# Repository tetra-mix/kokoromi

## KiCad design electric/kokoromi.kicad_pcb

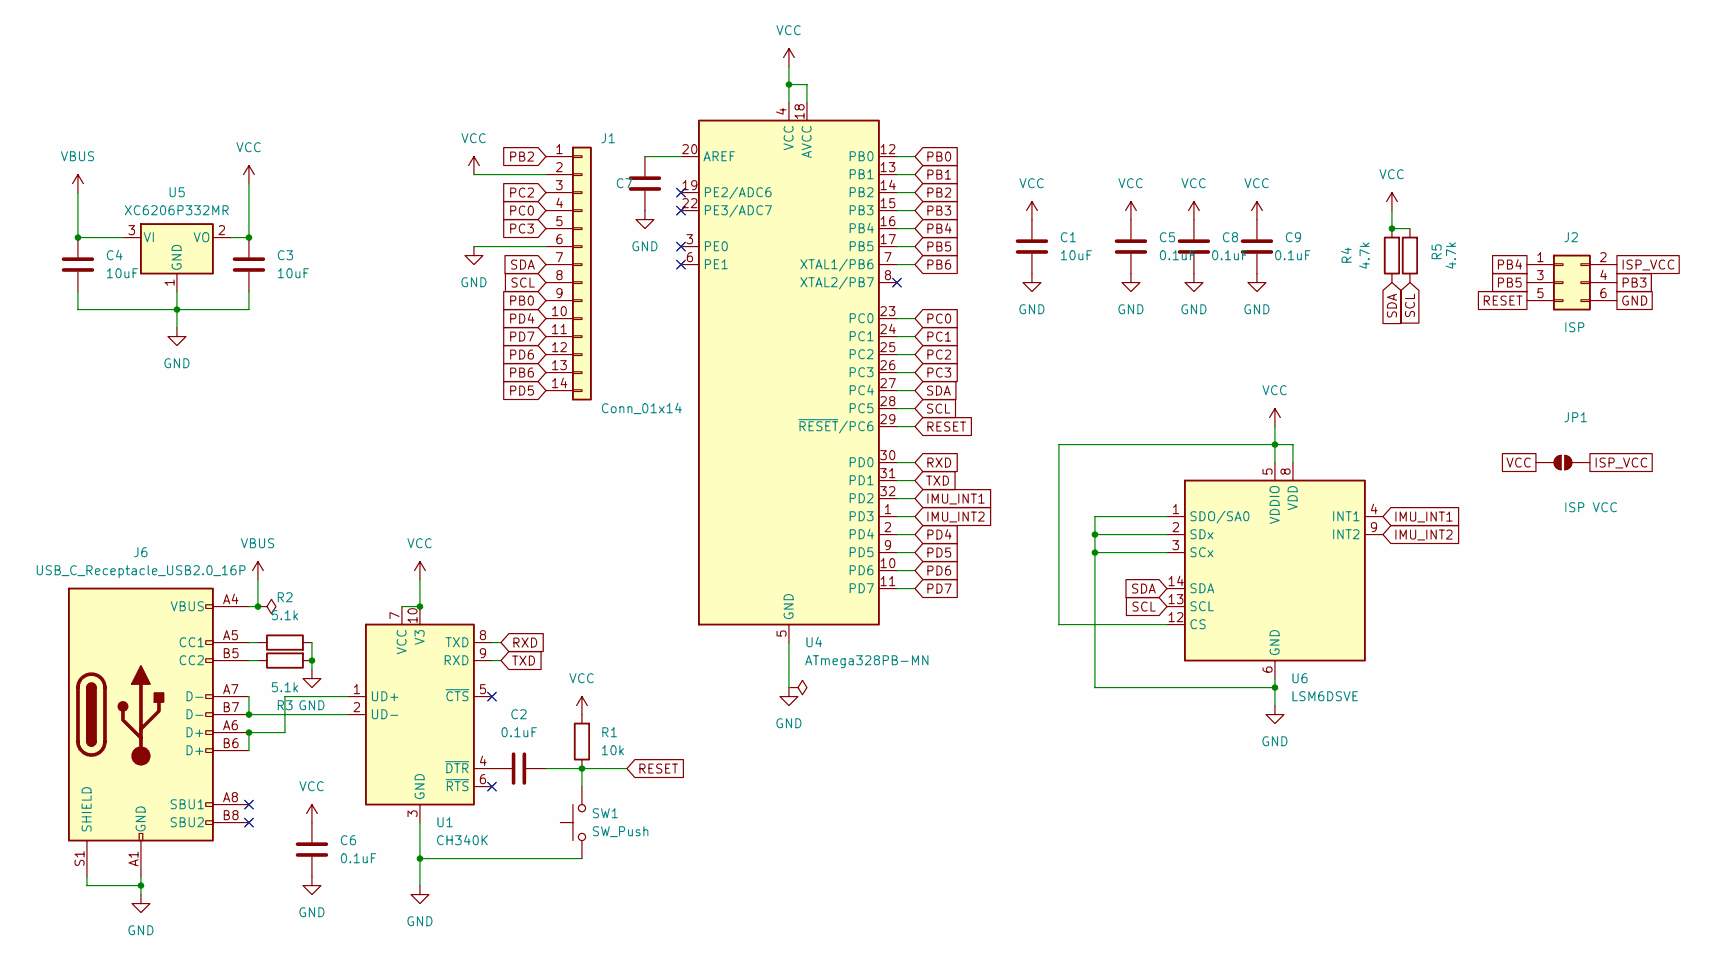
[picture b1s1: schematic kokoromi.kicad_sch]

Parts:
C1, C3: 10uF; C_0402_1005Metric; LCSC C15525
C2, C5, C6, C7, C8, C9: 0.1uF; C_0402_1005Metric; LCSC C1525
C4: 10uF; C_0603_1608Metric; LCSC C19702
J1: Conn_01x14; Pad_2x07_P2.54mm_Back
J2: ISP; PinHeader_2x03_P1.27mm_Vertical
J6: USB_C_Receptacle_USB2.0_16P; USB_C_Receptacle_HCTL_HC-TYPE-C-16P-01A; LCSC C2894897
JP1: ISP VCC; SolderJumper-2_P1.3mm_Open_RoundedPad1.0x1.5mm
R1: 10k; R_0402_1005Metric; LCSC C25744
R2, R3: 5.1k; R_0402_1005Metric; LCSC C25905
R4, R5: 4.7k; R_0402_1005Metric; LCSC C25900
SW1: SW_Push; SW_SPST_TS-1088-xR020; LCSC C720477
U1: CH340K; SSOP-10-1EP_3.9x4.9mm_P1mm_EP2.1x3.3mm_ShortToe; LCSC C968586
U4: ATmega328PB-MN; QFN-32-1EP_5x5mm_P0.5mm_EP3.1x3.1mm; LCSC C1337164
U5: XC6206P332MR; SOT-23-3; LCSC C5446
U6: LSM6DSVE; LGA-14_3x2.5mm_P0.5mm_LayoutBorder3x4y; LCSC C41785564

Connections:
GND: C1.2, C3.1, C4.1, C5.2, C6.2, C7.2, C8.2, C9.2, J1.6, J2.6, J6.A1 (GND), J6.A12 (GND), J6.B1 (GND), J6.B12 (GND), J6.S1 (SHIELD), R2.2, R3.2, SW1.1, U1.3 (GND), U1.11 (GND), U4.5 (GND), U4.21 (GND), U4.33 (GND), U5.1 (GND), U6.1 (SDO/SA0), U6.2 (SDX), U6.3 (SCX), U6.6 (GND), U6.7 (GND)
IMU_INT1: U4.32 (PD2), U6.4 (INT1)
IMU_INT2: U4.1 (PD3), U6.9 (INT2)
ISP_VCC: J2.2, JP1.2 (B)
unnamed: J6.A5 (CC1), R2.1
unnamed: J6.B5 (CC2), R3.1
unnamed: J6.A6 (D+), J6.B6 (D+), U1.1 (UD+)
unnamed: J6.A7 (D-), J6.B7 (D-), U1.2 (UD-)
unnamed: C2.1, U1.4 (~DTR)
unnamed: C7.1, U4.20 (AREF)
PB0: J1.9, U4.12 (PB0)
PB1: U4.13 (PB1)
PB2: J1.1, U4.14 (PB2)
PB3: J2.4, U4.15 (PB3)
PB4: J2.1, U4.16 (PB4)
PB5: J2.3, U4.17 (PB5)
PB6: J1.13, U4.7 (XTAL1/PB6)
PC0: J1.4, U4.23 (PC0)
PC1: U4.24 (PC1)
PC2: J1.3, U4.25 (PC2)
PC3: J1.5, U4.26 (PC3)
PD4: J1.10, U4.2 (PD4)
PD5: J1.14, U4.9 (PD5)
PD6: J1.12, U4.10 (PD6)
PD7: J1.11, U4.11 (PD7)
RESET: C2.2, J2.5, R1.1, SW1.2, U4.29 (~RESET/PC6)
RXD: U1.8 (TXD), U4.30 (PD0)
SCL: J1.8, R5.1, U4.28 (PC5), U6.13 (SCL)
SDA: J1.7, R4.1, U4.27 (PC4), U6.14 (SDA)
TXD: U1.9 (RXD), U4.31 (PD1)
VBUS: C4.2, J6.A4 (VBUS), J6.A9 (VBUS), J6.B4 (VBUS), J6.B9 (VBUS), U5.3 (VI)
VCC: C1.1, C3.2, C5.1, C6.1, C8.1, C9.1, J1.2, JP1.1 (A), R1.2, R4.2, R5.2, U1.7 (VCC), U1.10 (V3), U4.4 (VCC), U4.18 (AVCC), U5.2 (VO), U6.5 (VDDIO), U6.8 (VDD), U6.12 (CS)

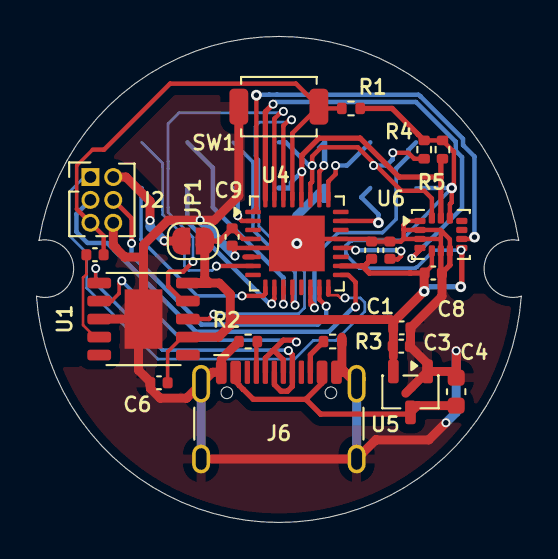
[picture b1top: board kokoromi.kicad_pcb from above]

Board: 2 copper layers, 26.9 x 27.0 mm, 23 parts (1 on the bottom side), 30 nets.

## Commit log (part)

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2026-05-01 init
2026-05-01 update: README.md
2026-05-01 update: add .DS_store in gitignre
